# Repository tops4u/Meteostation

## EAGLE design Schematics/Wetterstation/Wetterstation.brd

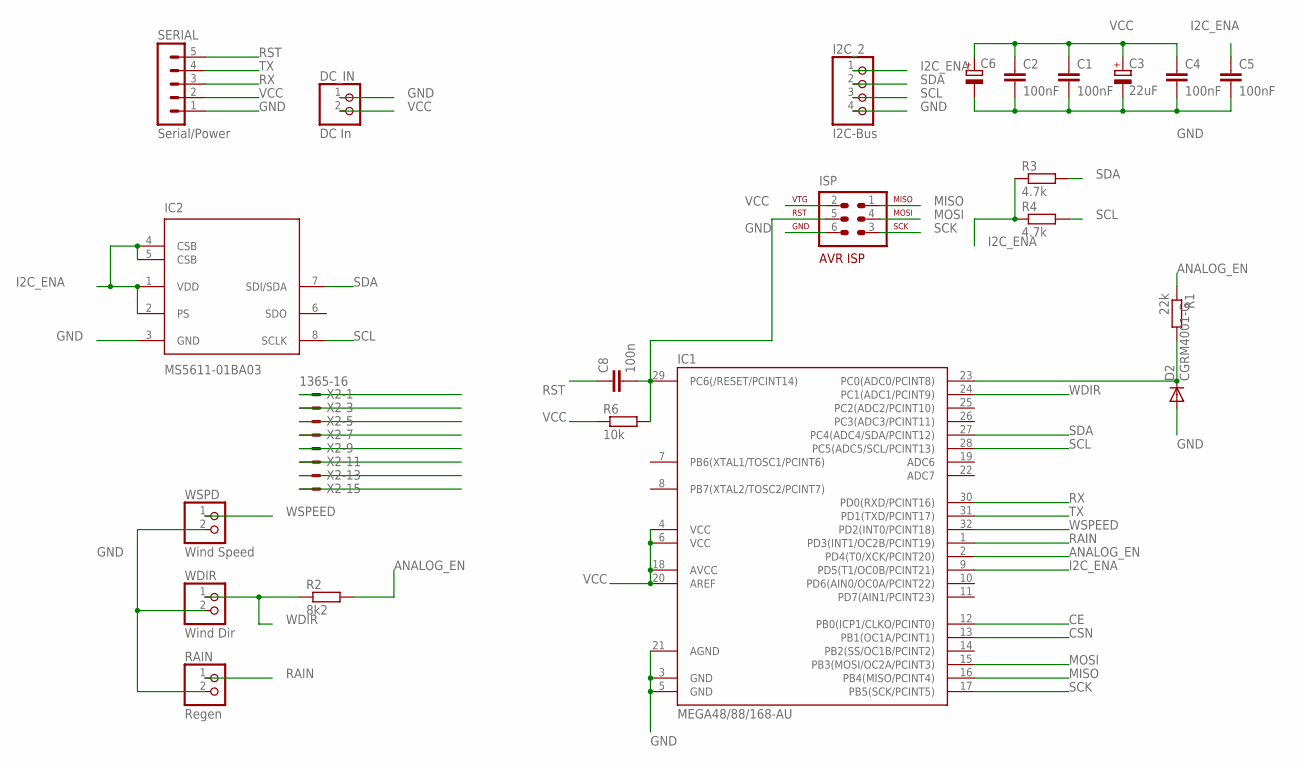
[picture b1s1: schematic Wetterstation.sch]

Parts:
C1, C2, C4, C5: 100nF; C0805
C3: 22uF; SMC_C
C6: CPOL-EUB/3528-21R; B/3528-21R
C8: 100n; C0805
D2: CGRM4001-G; SOD-123_MINI-SMA
DC_IN: DC In; 1X02
I2C_2: I2C-Bus; 1X04
IC1: MEGA48/88/168-AU; TQFP32-08
IC2: MS5611-01BA03; SON125P300X500X100-8N
ISP: AVR-ISP-6
R1: 22k; R1206
R2: 8k2; R1206
R3, R4: 4.7k; R1206
R6: 10k; R1206
RAIN: Regen; 1X02
SERIAL: Serial/Power; MA05-1
WDIR: Wind Dir; 1X02
WSPD: Wind Speed; 1X02
X2: 1365-16

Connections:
ANALOG_EN: IC1.2 (PD4(T0/XCK/PCINT20)), R1.1, R2.2
CE: IC1.12 (PB0(ICP1/CLKO/PCINT0)), X2.3
CSN: IC1.13 (PB1(OC1A/PCINT1)), X2.5
GND: C1.2, C2.2, C3.-, C4.2, C5.2, C6.-, D2.A, DC_IN.1, I2C_2.4, IC1.3 (GND), IC1.5 (GND), IC1.21 (AGND), IC2.3 (GND), ISP.6, RAIN.2, SERIAL.1, WDIR.2, WSPD.2, X2.15
I2C_ENA: C5.1, I2C_2.1, IC1.9 (PD5(T1/OC0B/PCINT21)), IC2.1 (VDD), IC2.2 (PS), IC2.4 (CSB), IC2.5 (CSB), R3.1, R4.1
IRQ: X2.13
MISO: IC1.16 (PB4(MISO/PCINT4)), ISP.1, X2.11
MOSI: IC1.15 (PB3(MOSI/OC2A/PCINT3)), ISP.4, X2.9
unnamed: C8.2, IC1.29 (PC6(/RESET/PCINT14)), ISP.5, R6.2
RAIN: IC1.1 (PD3(INT1/OC2B/PCINT19)), RAIN.1
RST: C8.1, SERIAL.5
RX: IC1.30 (PD0(RXD/PCINT16)), SERIAL.3
SCK: IC1.17 (PB5(SCK/PCINT5)), ISP.3, X2.7
SCL: I2C_2.3, IC1.28 (PC5(ADC5/SCL/PCINT13)), IC2.8 (SCLK), R4.2
SDA: I2C_2.2, IC1.27 (PC4(ADC4/SDA/PCINT12)), IC2.7 (SDI/SDA), R3.2
TX: IC1.31 (PD1(TXD/PCINT17)), SERIAL.4
VCC: C1.1, C2.1, C3.+, C4.1, C6.+, DC_IN.2, IC1.4 (VCC), IC1.6 (VCC), IC1.18 (AVCC), IC1.20 (AREF), ISP.2, R6.1, SERIAL.2, X2.1
VCC_MEAS: D2.C, IC1.23 (PC0(ADC0/PCINT8)), R1.2
WDIR: IC1.24 (PC1(ADC1/PCINT9)), R2.1, WDIR.1
WSPEED: IC1.32 (PD2(INT0/PCINT18)), WSPD.1

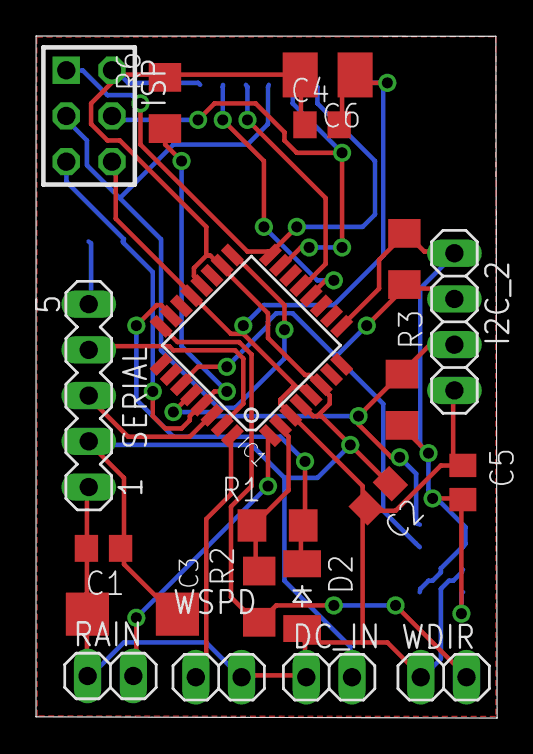
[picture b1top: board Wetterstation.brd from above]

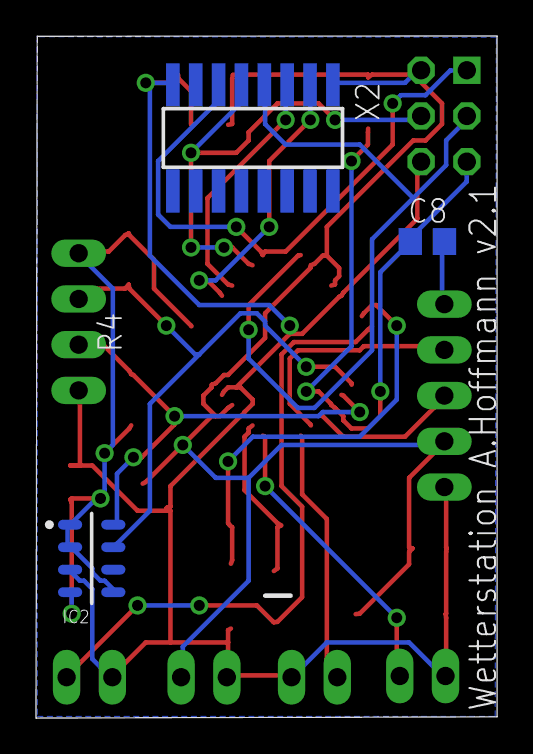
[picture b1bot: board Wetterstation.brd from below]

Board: 2 copper layers, 25.6 x 37.9 mm, 23 parts (3 on the bottom side), 19 nets.

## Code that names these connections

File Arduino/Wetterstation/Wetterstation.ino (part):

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
// IO Pin Konfiguration
#define BATT_PIN 0
#define WDIR_PIN 1
#define WSPEED_PIN 2
#define RAIN_PIN 3
#define ANALOG_ENABLE 4
#define I2C_ENABLE 5
#define NRF_CE 8
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  fdevopen( &my_putc, 0);
  pinMode(I2C_ENABLE, OUTPUT);
  pinMode(ANALOG_ENABLE, OUTPUT);
  pinMode(WSPEED_PIN, INPUT_PULLUP);
  pinMode(RAIN_PIN, INPUT_PULLUP);
  for (int i = 7; i < 13; i++) {
    pinMode(i, OUTPUT);
    digitalWrite(i, false);
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}

void attachIRQs() {
  attachInterrupt(digitalPinToInterrupt(WSPEED_PIN), windUp, FALLING);
  attachInterrupt(digitalPinToInterrupt(RAIN_PIN), rainUp, CHANGE);
}

void detachIRQs() {
  detachInterrupt(digitalPinToInterrupt(WSPEED_PIN));
  detachInterrupt(digitalPinToInterrupt(RAIN_PIN));

}

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
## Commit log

2019-04-14 Initial Version with Outside Wetterstation.ino, Inside Keller.ino Arduinos and initial Raspberry HPMA Adapter
2019-04-14 Eagle Schematics

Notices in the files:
Arduino/Wetterstation/Wetterstation.ino:
Der vorliegende Code ist Open Source nach GPL
